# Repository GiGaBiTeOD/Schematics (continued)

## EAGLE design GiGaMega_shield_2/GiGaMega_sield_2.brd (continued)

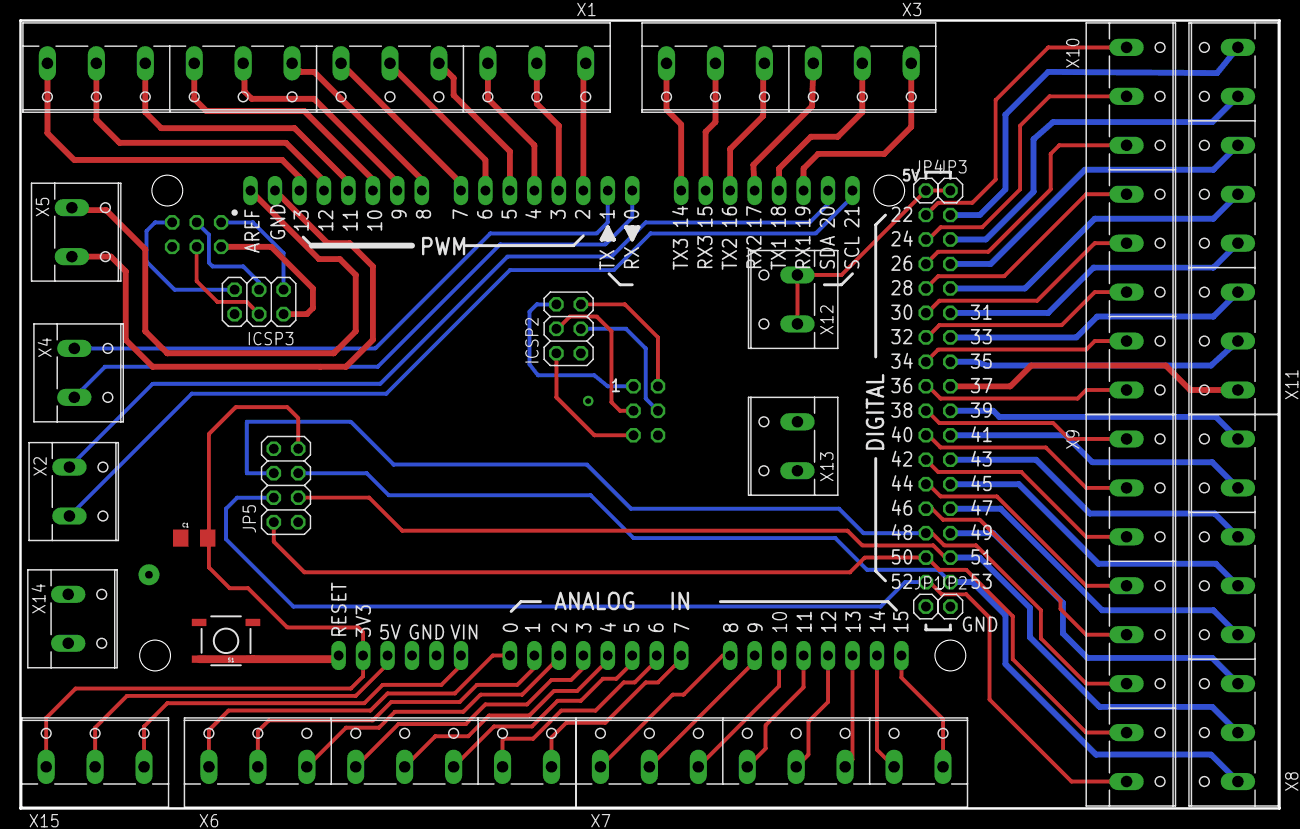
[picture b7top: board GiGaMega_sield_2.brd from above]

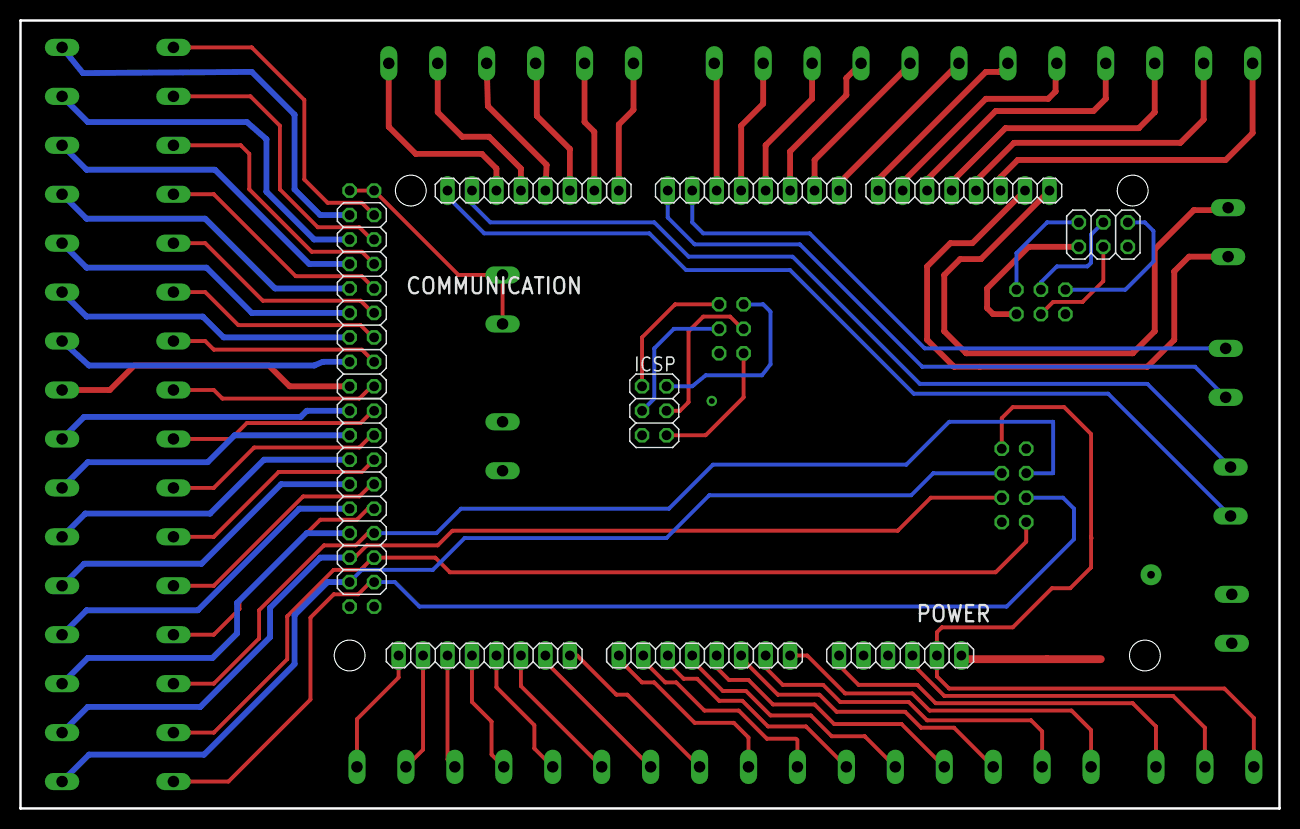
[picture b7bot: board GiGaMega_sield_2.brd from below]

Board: 2 copper layers, 130.7 x 81.8 mm, 34 parts (10 on the bottom side), 88 nets.

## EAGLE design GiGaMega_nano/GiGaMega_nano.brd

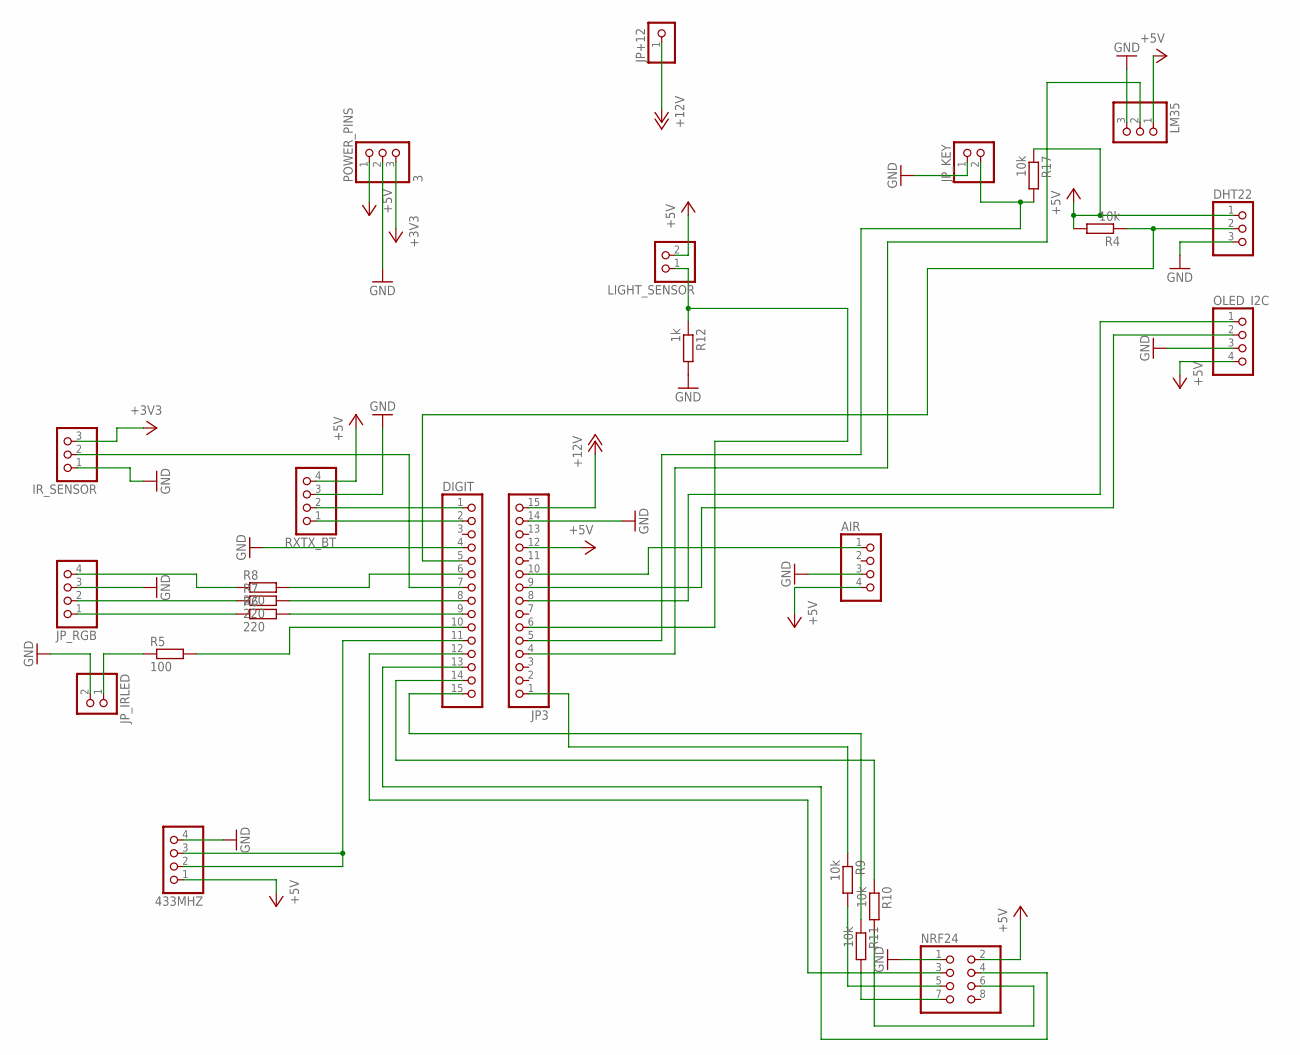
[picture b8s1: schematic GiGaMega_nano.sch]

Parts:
433MHZ: PINHD-1X4; 1X04
AIR: PINHD-1X4; 1X04
DHT22: PINHD-1X3; 1X03
DIGIT: PINHD-1X15; 1X15
IR_SENSOR: PINHD-1X3; 1X03
JP3: PINHD-1X15; 1X15
JP+12: PINHD-1X1; 1X01
JP_IRLED: PINHD-1X2; 1X02
JP_KEY: PINHD-1X2; 1X02
JP_RGB: PINHD-1X4; 1X04
LIGHT_SENSOR: PINHD-1X2; 1X02
LM35: PINHD-1X3; 1X03
NRF24: PINHD-2X4; 2X04
OLED_I2C: PINHD-1X4; 1X04
POWER_PINS: 3; 1X03
R4, R9, R10, R11, R17: 10k; R1206
R5: 100; R1206
R6, R7, R8: 220; R1206
R12: 1k; R1206
RXTX_BT: PINHD-1X4; 1X04

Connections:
+3V3: IR_SENSOR.3, POWER_PINS.3
+5V: 433MHZ.1, AIR.4, DHT22.1, JP3.12, LIGHT_SENSOR.2, LM35.1, NRF24.2, OLED_I2C.4, POWER_PINS.1, R4.2, R17.1, RXTX_BT.4
+12V: JP3.15, JP+12.1
BLUE: JP_RGB.1, R6.1
BLUE_6: DIGIT.9, R6.2
CE: DIGIT.12, NRF24.3
CSN: DIGIT.13, NRF24.4
GND: 433MHZ.4, AIR.3, DHT22.3, DIGIT.4, IR_SENSOR.1, JP3.14, JP_IRLED.2, JP_KEY.1, JP_RGB.3, LM35.3, NRF24.1, OLED_I2C.3, POWER_PINS.2, R12.2, RXTX_BT.3
GREEN: JP_RGB.2, R7.1
GREEN_5: DIGIT.8, R7.2
KEY_PIN: JP3.5, JP_KEY.2, R17.2
MISO: DIGIT.15, R11.1
MOSI: DIGIT.14, R10.1
unnamed: JP3.1, R9.1
unnamed: JP_IRLED.1, R5.1
unnamed: 433MHZ.2, 433MHZ.3, DIGIT.11
unnamed: AIR.1, JP3.10
unnamed: DIGIT.7, IR_SENSOR.2
unnamed: DIGIT.10, R5.2
unnamed: NRF24.6, R10.2
unnamed: NRF24.7, R11.2
unnamed: NRF24.5, R9.2
PIN13: DHT22.2, DIGIT.5, R4.1
PIN23: JP3.6, LIGHT_SENSOR.1, R12.1
PIN25: JP3.4, LM35.2
RED: JP_RGB.4, R8.1
RED_3: DIGIT.6, R8.2
RX: DIGIT.2, RXTX_BT.1
SCL: JP3.9, OLED_I2C.2
SDA: JP3.8, OLED_I2C.1
TX: DIGIT.1, RXTX_BT.2

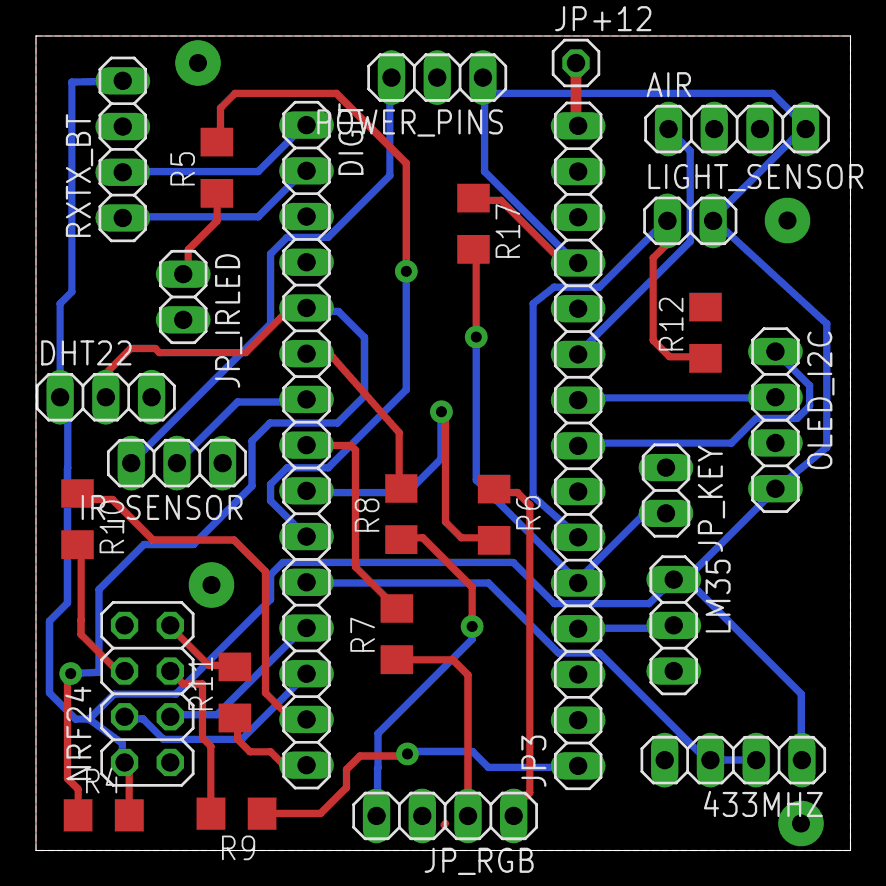
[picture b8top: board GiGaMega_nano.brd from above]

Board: 2 copper layers, 45.2 x 45.2 mm, 26 parts (0 on the bottom side), 31 nets.

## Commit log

2017-03-19 :lollipop: Added .gitattributes & .gitignore files
2017-03-21 added new schematicks
2017-03-21 changed keyboard schematic
2017-03-22 finished layout
2017-04-17 Correct SPI connectors
2017-04-17 corrected connect button
2017-04-17 added new schematics
2017-08-20 added port extender, modified relay shield
2018-05-04 some changes
2018-05-04 some changes 1
2018-05-04 add fritzing scheme
2018-06-05 universal 2 added sensor connectors
2018-06-11 add pinouts
2018-06-21 connect i2c devices
2018-06-21 add I2C devices fix incorrect commit
2018-07-23 changed power board
2018-08-28 changed power scheme
2018-08-28 added sensors connection
2018-08-31 add IR, LIGHT 433, 315 sensors
2018-09-03 added all sensors
2018-09-16 schematic alpha
2018-11-06 added schematic for terrarium control
